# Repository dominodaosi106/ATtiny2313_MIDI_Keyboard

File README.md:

# ATtiny2313_MIDI_Keyboard
# MIDIコントローラ基板 取扱説明書(ver1用）

## 概要
このMIDIコントローラ基板は、ATtiny2313Aマイクロコントローラを搭載し、MIDI信号を送信して楽器やソフトウェアを制御するためのデバイスです。以下の機能を提供します：
- 12個のノートボタン（C, C#, D, D#, E, F, F#, G, G#, A, A#, B）による音階の発音
- MIDIチャンネル選択（1～16）
- オクターブシフト機能（-5～+3オクターブ）
- プログラムチェンジ（ピアノ、オルゴール、矩形波、ベース+リード）
- MIDIチャンネル10でのオクターブシフトロック機能

電源を入れると、初期設定に基づいてMIDIチャンネルと基準ノートが設定され、ボタン操作で音を鳴らしたり設定を変更したりできます。

## 操作方法

### 1. 基本操作
- **ノートボタン（C, C#, D, D#, E, F, F#, G, G#, A, A#, B）**：
  - 押す：対応する音階をMIDI信号として発音（ベロシティ127）。
  - 離す：発音開始時の音階を停止。
  - 例：Cボタンを押してC4が鳴り、オクターブシフト後に離すとC4が停止。
- **オクターブシフト（UP/DOWNボタン）**：
  - **短押し（200ms未満）**：押すと即時にオクターブが上下し、離してもシフトを維持。
  - **長押し（200ms以上）**：押すと即時にオクターブが上下し、離すと元のオクターブに戻る。
  - 範囲：-5～+3オクターブ（例：C4→C-1～C7）。
- **ファンクションキー（UP+DOWN同時押し）**：
  - UPとDOWNボタンを同時に押すと、ファンクションキーモードに移行。
  - 他のボタン（C#, D#, F#, A#, C, D, A, B）を押して各種設定を変更。
  - どちらかのボタンを離すと通常モードに戻る。

### 2. ファンクションキーモードでの操作
ファンクションキーモード（UP+DOWN同時押し）で以下の操作が可能です：
- **MIDIチャンネル変更**：
  - **C#**：MIDIチャンネル1（基準ノート：C4）に設定。
  - **D#**：MIDIチャンネル10に設定（基準ノートは現在の値を保持）。
  - **F#**：MIDIチャンネルを1つ下げる（1～16、基準ノートは保持）。
  - **A#**：MIDIチャンネルを1つ上げる（1～16、基準ノートは保持）。
- **プログラムチェンジ**：
  - **C**：プログラム1（ピアノ）に変更。
  - **D**：プログラム10（オルゴール）に変更。
  - **A**：プログラム88（ベース+リード）に変更。
  - **B**：プログラム81（矩形波）に変更。

### 3. 初期設定
- **MIDIチャンネルと基準ノート**：
  - 起動時のCHピンの状態で初期設定：
    - CHピンがLOW：MIDIチャンネル1、基準ノートC4（60）。
    - CHピンがHIGH：MIDIチャンネル10、基準ノートC2（36）。
- **オクターブシフト**：
  - 初期値は0（基準ノートそのまま）。
  - MIDIチャンネル10でMODEピンがHIGHの場合、オクターブシフトは無効（常に0）。

### 4. 注意事項
- **オクターブシフト中の発音**：
  - ノートボタンを押している間にオクターブシフトしても、発音中の音は継続。
  - ノートボタンを離すと、押した時点の音階（例：C4）が停止。
  - 新たに押したノートは現在のオクターブシフトを反映（例：C5）。
- **MIDIチャンネル変更**：
  - CH1からCH10に変更しても、現在の基準ノート（例：C4やC6）が保持される。
  - CH1への変更（C#）では基準ノートがC4にリセット。
- **MODEピン（MIDIチャンネル10）**：
  - MODEピンがHIGHの場合、オクターブシフトが無効化され、基準ノート（C2など）で固定。
- **デバウンス**：
  - ボタン操作は10msのデバウンス処理済み。素早い連打でも安定動作。
- **電源**：
  - 電源投入後、CHピンの状態を即座に読み込み。
  - MIDI機器に正しく接続してください（MIDI OUT端子を使用）。

### 5. トラブルシューティング
- **音が出ない**：
  - MIDIケーブルが正しく接続されているか確認。
  - MIDIチャンネルが受信機器と一致しているか確認（C#, D#, F#, A#で変更）。
  - プログラムチェンジが適切か確認（C, D, A, Bで変更）。
- **オクターブシフトが効かない**：
  - MIDIチャンネル10でMODEピンがHIGHでないか確認（HIGHでシフト無効）。
  - UP/DOWNボタンの短押し/長押しを試す。
- **意図しない音階が鳴る**：
  - 現在の基準ノートとオクターブシフトを確認（CH1: C4ベース、CH10: C2ベース）。
  - ファンクションキー+C#でCH1（C4）にリセット可能。

## 仕様
- **マイクロコントローラ**：ATtiny2313A（内蔵1MHzクロック）
- **ビルド環境**：Atmel Studio 7 (Version: 7.0.129)
- **MIDIボーレート**：31,250bps（標準）
- **電源**：5V（VCC-GND間）
- **ボタン**：12ノートボタン、2シフトボタン（UP/DOWN）、2設定ピン（CH, MODE）

---

ご不明点やサポートが必要な場合は、開発者にご連絡ください。

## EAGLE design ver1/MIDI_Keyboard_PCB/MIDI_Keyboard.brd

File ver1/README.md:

# ATtiny2313_MIDI_Keyboard
## MIDIコントローラ基板 取扱説明書

## 概要
このMIDIコントローラ基板は、ATtiny2313Aマイクロコントローラを搭載し、MIDI信号を送信して楽器やソフトウェアを制御するためのデバイスです。以下の機能を提供します：
- 12個のノートボタン（C, C#, D, D#, E, F, F#, G, G#, A, A#, B）による音階の発音
- MIDIチャンネル選択（1～16）
- オクターブシフト機能（-5～+3オクターブ）
- プログラムチェンジ（ピアノ、オルゴール、矩形波、ベース+リード）
- MIDIチャンネル10でのオクターブシフトロック機能

電源を入れると、初期設定に基づいてMIDIチャンネルと基準ノートが設定され、ボタン操作で音を鳴らしたり設定を変更したりできます。

## 操作方法

### 1. 基本操作
- **ノートボタン（C, C#, D, D#, E, F, F#, G, G#, A, A#, B）**：
  - 押す：対応する音階をMIDI信号として発音（ベロシティ127）。
  - 離す：発音開始時の音階を停止。
  - 例：Cボタンを押してC4が鳴り、オクターブシフト後に離すとC4が停止。
- **オクターブシフト（UP/DOWNボタン）**：
  - **短押し（200ms未満）**：押すと即時にオクターブが上下し、離してもシフトを維持。
  - **長押し（200ms以上）**：押すと即時にオクターブが上下し、離すと元のオクターブに戻る。
  - 範囲：-5～+3オクターブ（例：C4→C-1～C7）。
- **ファンクションキー（UP+DOWN同時押し）**：
  - UPとDOWNボタンを同時に押すと、ファンクションキーモードに移行。
  - 他のボタン（C#, D#, F#, A#, C, D, A, B）を押して各種設定を変更。
  - どちらかのボタンを離すと通常モードに戻る。

### 2. ファンクションキーモードでの操作
ファンクションキーモード（UP+DOWN同時押し）で以下の操作が可能です：
- **MIDIチャンネル変更**：
  - **C#**：MIDIチャンネル1（基準ノート：C4）に設定。
  - **D#**：MIDIチャンネル10に設定（基準ノートは現在の値を保持）。
  - **F#**：MIDIチャンネルを1つ下げる（1～16、基準ノートは保持）。
  - **A#**：MIDIチャンネルを1つ上げる（1～16、基準ノートは保持）。
- **プログラムチェンジ**：
  - **C**：プログラム1（ピアノ）に変更。
  - **D**：プログラム10（オルゴール）に変更。
  - **A**：プログラム88（ベース+リード）に変更。
  - **B**：プログラム81（矩形波）に変更。

### 3. 初期設定
- **MIDIチャンネルと基準ノート**：
  - 起動時のCHピンの状態で初期設定：
    - CHピンがLOW：MIDIチャンネル1、基準ノートC4（60）。
    - CHピンがHIGH：MIDIチャンネル10、基準ノートC2（36）。
- **オクターブシフト**：
  - 初期値は0（基準ノートそのまま）。
  - MIDIチャンネル10でMODEピンがHIGHの場合、オクターブシフトは無効（常に0）。

### 4. 注意事項
- **オクターブシフト中の発音**：
  - ノートボタンを押している間にオクターブシフトしても、発音中の音は継続。
  - ノートボタンを離すと、押した時点の音階（例：C4）が停止。
  - 新たに押したノートは現在のオクターブシフトを反映（例：C5）。
- **MIDIチャンネル変更**：
  - CH1からCH10に変更しても、現在の基準ノート（例：C4やC6）が保持される。
  - CH1への変更（C#）では基準ノートがC4にリセット。
- **MODEピン（MIDIチャンネル10）**：
  - MODEピンがHIGHの場合、オクターブシフトが無効化され、基準ノート（C2など）で固定。
- **デバウンス**：
  - ボタン操作は10msのデバウンス処理済み。素早い連打でも安定動作。
- **電源**：
  - 電源投入後、CHピンの状態を即座に読み込み。
  - MIDI機器に正しく接続してください（MIDI OUT端子を使用）。

### 5. トラブルシューティング
- **音が出ない**：
  - MIDIケーブルが正しく接続されているか確認。
  - MIDIチャンネルが受信機器と一致しているか確認（C#, D#, F#, A#で変更）。
  - プログラムチェンジが適切か確認（C, D, A, Bで変更）。
- **オクターブシフトが効かない**：
  - MIDIチャンネル10でMODEピンがHIGHでないか確認（HIGHでシフト無効）。
  - UP/DOWNボタンの短押し/長押しを試す。
- **意図しない音階が鳴る**：
  - 現在の基準ノートとオクターブシフトを確認（CH1: C4ベース、CH10: C2ベース）。
  - ファンクションキー+C#でCH1（C4）にリセット可能。

## 仕様
- **マイクロコントローラ**：ATtiny2313A（内蔵1MHzクロック）
- **ビルド環境**：Atmel Studio 7 (Version: 7.0.129)
- **MIDIボーレート**：31,250bps（標準）
- **電源**：5V（VCC-GND間）
- **ボタン**：12ノートボタン、2シフトボタン（UP/DOWN）、2設定ピン（CH, MODE）

---

ご不明点やサポートが必要な場合は、開発者にご連絡ください。

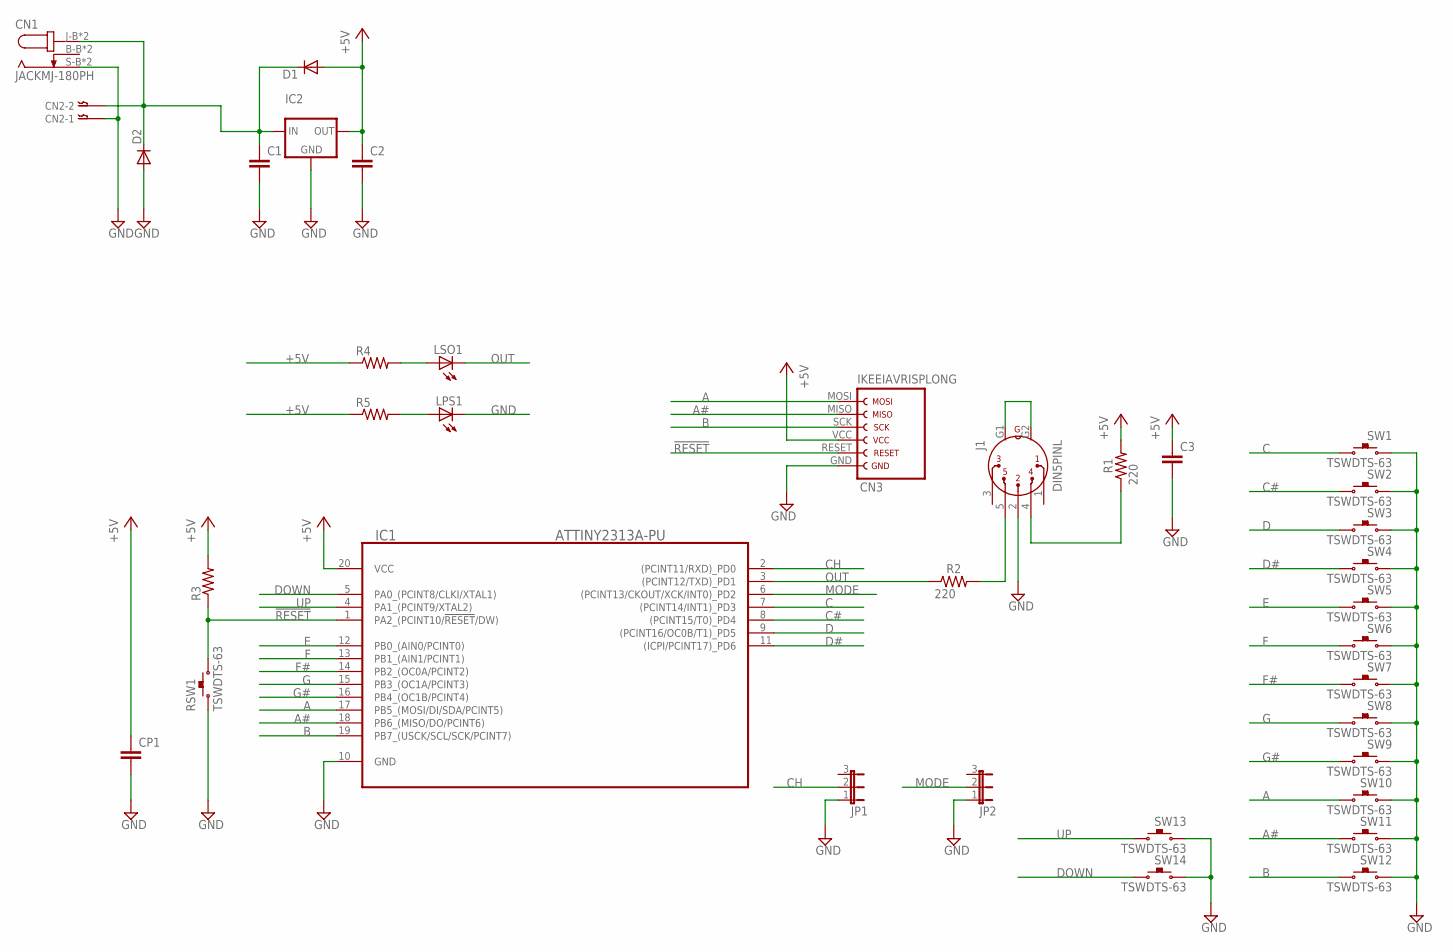
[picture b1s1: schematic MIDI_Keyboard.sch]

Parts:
C1, C2, C3: C-EU025-025X050; C025-025X050
CN1: JACKMJ-180PH; MJ-179PH
CN2: B2B-XH-A
CN3: IKEEIAVRISPLONG; IKEEIAVRISP
CP1: C-EU025-025X050; C025-025X050
D1, D2: 1N4148DO35-10R; DO35-10R
IC1: ATTINY2313A-PU; DIP254P762X533-20
IC2: 78LXXL; TO92LINE
J1: DIN5PINL
JP1, JP2: JP2E; JP2
LPS1: LED3MM
LSO1: LED3MM
R1, R2: 220; 0207/10
R3, R4, R5: R-US_0207/10; 0207/10
RSW1: TSWDTS-63; DTS-63
SW1, SW2, SW3, SW4, SW5, SW6, SW7, SW8, SW9, SW10, SW11, SW12, SW13, SW14: TSWDTS-63; DTS-63

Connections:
!RESET: CN3.RESET, IC1.1 (PA2_(PCINT10/!RESET!/DW)), R3.1, RSW1.1, RSW1.2 (1)
+5V: C2.1, C3.1, CN3.VCC, CP1.1, D1.A, IC1.20 (VCC), IC2.1 (OUT), R1.2, R3.2, R4.1, R5.1
A: CN3.MOSI, IC1.17 (PB5_(MOSI/DI/SDA/PCINT5)), SW10.1, SW10.2 (1)
A#: CN3.MISO, IC1.18 (PB6_(MISO/DO/PCINT6)), SW11.1, SW11.2 (1)
B: CN3.SCK, IC1.19 (PB7_(USCK/SCL/SCK/PCINT7)), SW12.1, SW12.2 (1)
C: IC1.7 ((PCINT14/INT1)_PD3), SW1.1, SW1.2 (1)
C#: IC1.8 ((PCINT15/T0)_PD4), SW2.1, SW2.2 (1)
CH: IC1.2 ((PCINT11/RXD)_PD0), JP1.2
D: IC1.9 ((PCINT16/OC0B/T1)_PD5), SW3.1, SW3.2 (1)
D#: IC1.11 ((ICPI/PCINT17)_PD6), SW4.1, SW4.2 (1)
DOWN: IC1.5 (PA0_(PCINT8/CLKI/XTAL1)), SW14.1, SW14.2 (1)
E: IC1.12 (PB0_(AIN0/PCINT0)), SW5.1, SW5.2 (1)
F: IC1.13 (PB1_(AIN1/PCINT1)), SW6.1, SW6.2 (1)
F#: IC1.14 (PB2_(OC0A/PCINT2)), SW7.1, SW7.2 (1)
G: IC1.15 (PB3_(OC1A/PCINT3)), SW8.1, SW8.2 (1)
G#: IC1.16 (PB4_(OC1B/PCINT4)), SW9.1, SW9.2 (1)
GND: C1.2, C2.2, C3.2, CN1.S-B (1), CN1.S-T (1), CN2.1, CN3.GND, CP1.2, D2.A, IC1.10 (GND), IC2.2 (GND), J1.2, JP1.1, JP2.1, LPS1.K (C), RSW1.3 (2), RSW1.4 (2), SW1.3 (2), SW1.4 (2), SW2.3 (2), SW2.4 (2), SW3.3 (2), SW3.4 (2), SW4.3 (2), SW4.4 (2), SW5.3 (2), SW5.4 (2), SW6.3 (2), SW6.4 (2), SW7.3 (2), SW7.4 (2), SW8.3 (2), SW8.4 (2), SW9.3 (2), SW9.4 (2), SW10.3 (2), SW10.4 (2), SW11.3 (2), SW11.4 (2), SW12.3 (2), SW12.4 (2), SW13.3 (2), SW13.4 (2), SW14.3 (2), SW14.4 (2)
MODE: IC1.6 ((PCINT13/CKOUT/XCK/INT0)_PD2), JP2.2
unnamed: J1.4, R1.1
unnamed: J1.5, R2.2
unnamed: J1.G1, J1.G2
unnamed: LSO1.A, R4.2
unnamed: LPS1.A, R5.2
unnamed: C1.1, CN1.J-B (3), CN1.J-T (3), CN2.2, D1.C, D2.C, IC2.3 (IN)
OUT: IC1.3 ((PCINT12/TXD)_PD1), LSO1.K (C), R2.1
UP: IC1.4 (PA1_(PCINT9/XTAL2)), SW13.1, SW13.2 (1)

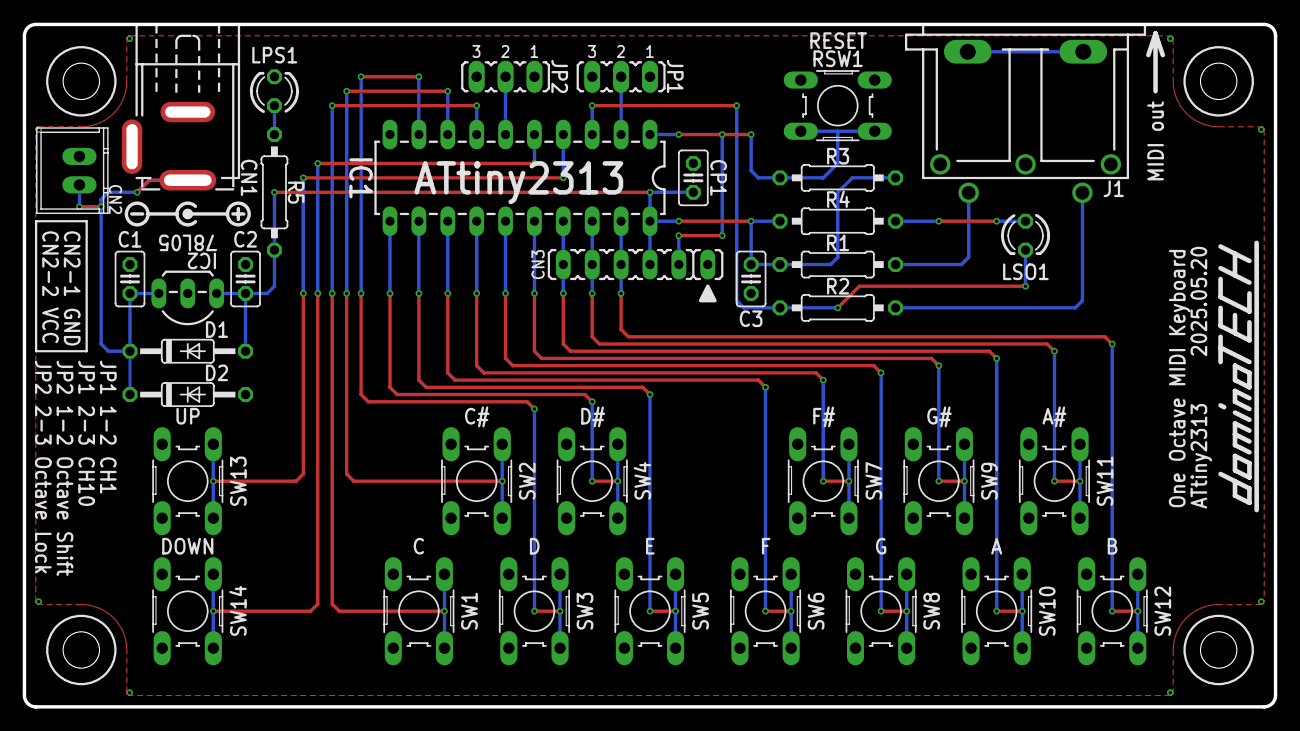
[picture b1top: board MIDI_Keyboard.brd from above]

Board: 2 copper layers, 109.3 x 59.3 mm, 36 parts (0 on the bottom side), 26 nets.

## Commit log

2025-05-27 main.c readme追加
2025-05-27 README更新
2025-05-27 回路図,基板データ追加
2025-05-27 hex追加
2025-05-27 main.c変更
